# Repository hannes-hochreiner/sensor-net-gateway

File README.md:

# Sensor Net Gateway
A gateway for translating messages from the sensor net sensors to USB CDC.

## Pre-Order PCB Checklist
  * [x] ground flood
  * [x] surround antenna traces with vias
  * [x] change LDO footprint
  * [x] change connector footprint
  * [x] interrupt lines
  * [x] diagram cleanup
  * [x] diagram check
  * [x] layout check

# Post Assembly Checks

## Electrical Check
On visual inspection, the connections looked pretty good.
To make sure nothing major went wrong, I checked for shorts, especially between power and ground.
I also checked that ground was connected to the right side of the electrolytic capacitor.

## FTDI
My first check of the FTDI chip was to simply connect the board and check the output of dmsg:
```
[862594.355360] Indeed it is in host mode hprt0 = 00021501
[862594.565069] usb 1-1: new full-speed USB device number 2 using dwc_otg
[862594.565389] Indeed it is in host mode hprt0 = 00021501
[862594.812139] usb 1-1: New USB device found, idVendor=0403, idProduct=6015, bcdDevice=10.00
[862594.812159] usb 1-1: New USB device strings: Mfr=1, Product=2, SerialNumber=3
[862594.812168] usb 1-1: Product: FT230X Basic UART
[862594.812176] usb 1-1: Manufacturer: FTDI
[862594.812184] usb 1-1: SerialNumber: DM01KPIW
[862594.947315] usbcore: registered new interface driver usbserial_generic
[862594.947420] usbserial: USB Serial support registered for generic
[862594.963184] usbcore: registered new interface driver ftdi_sio
[862594.963293] usbserial: USB Serial support registered for FTDI USB Serial Device
[862594.963573] ftdi_sio 1-1:1.0: FTDI USB Serial Device converter detected
[862594.963800] usb 1-1: Detected FT-X
[862594.997482] usb 1-1: FTDI USB Serial Device converter now attached to ttyUSB0
```
## Power
Next, I checked the power rail after the two-stage conversion.
I got 2.75 V, which is a bit lower than expected, but within specification (2.8 V +/- 3%) and still ok for my use.

## UART communication
UART communication without hardware flow control worked fine, after I switched TX and RX (see [issue TX-RX and CTS-RTS inverted](#TX-RX-and-CTS-RTS-inverted) below).
I have tried running the interface at 10 kHz, 100 kHz, and 1 MHz.
So far, I was only successful at 10 kHz.
My suspicion is that the internal high-speed clock of the STM32 is not precise enough.

## RFM98
The RFM98 works as expected.
The RSSI is around -95 dBm, which is lower than I hoped.
With the breakout board and a different antenna, I have seen a typical RSSI around -65 dBm.
So there is some potential for improvement here by using different antennas.
Since the module claims to have a sensitivity down to -148 dBm, I think I should be fine.
From what I have seen, most of the sensor transmissions were picked up.

## Authentication chip
So far, I have not been able to convince the authentication chip to respond.
I have tried different addresses and also implemented the wake-up sequence.
My suspicion is that I did not properly solder it.

## External oscillator
I could not get a stable signal from the external oscillator.
Probably also a case for re-soldering.

# Issues
## TX-RX and CTS-RTS inverted
When I wired up the schematic, I made the mistake to connect TX to TX, RX to RX, and so on.
While this works fine for SPI and I2C, it does not work for UART.
With UART, TX has to be connected to RX and CTS to RTS.
The saving grace is that the STM32 has an option to swap TX and RX lines.
Seems that I am not the first one to make this mistake :-).

CTS and RTS cannot be swapped in the chip, so in this iteration I won't be able to use the integrated hardware flow control.
Since I am using the UART interface based on interrupts, it should be easily possible to set the RTS and CTS lines manually.

## Cut-outs seem off
The PCB fits fine into the case, but the margins are not uniform.
Therefore, I want to go back and check the cut-outs.

# Hardware to order
## Screws
Self-tapping screws [Amazon link](https://www.amazon.de/Baoyl-Office-Cutting-Tapping-Printer-Accessories/dp/B07VX7XYYC/ref=sr_1_8?__mk_de_DE=%C3%85M%C3%85%C5%BD%C3%95%C3%91&keywords=M3%2Bself-tapping%2Bscrews&qid=1567273654&s=gateway&sr=8-8&th=1)

## Hub
USB-hub [Amazon link](https://www.amazon.de/CSL-aktiver-schaltbar-Verteiler-Notebook/dp/B07F2Q94CT/ref=sr_1_41?__mk_de_DE=%C3%85M%C3%85%C5%BD%C3%95%C3%91&crid=22QNN2JE5YY1E&keywords=usb+hub+aktiv+3.0+mit+netzteil&qid=1567355394&s=gateway&sprefix=usb+hub%2Caps%2C195&sr=8-41)

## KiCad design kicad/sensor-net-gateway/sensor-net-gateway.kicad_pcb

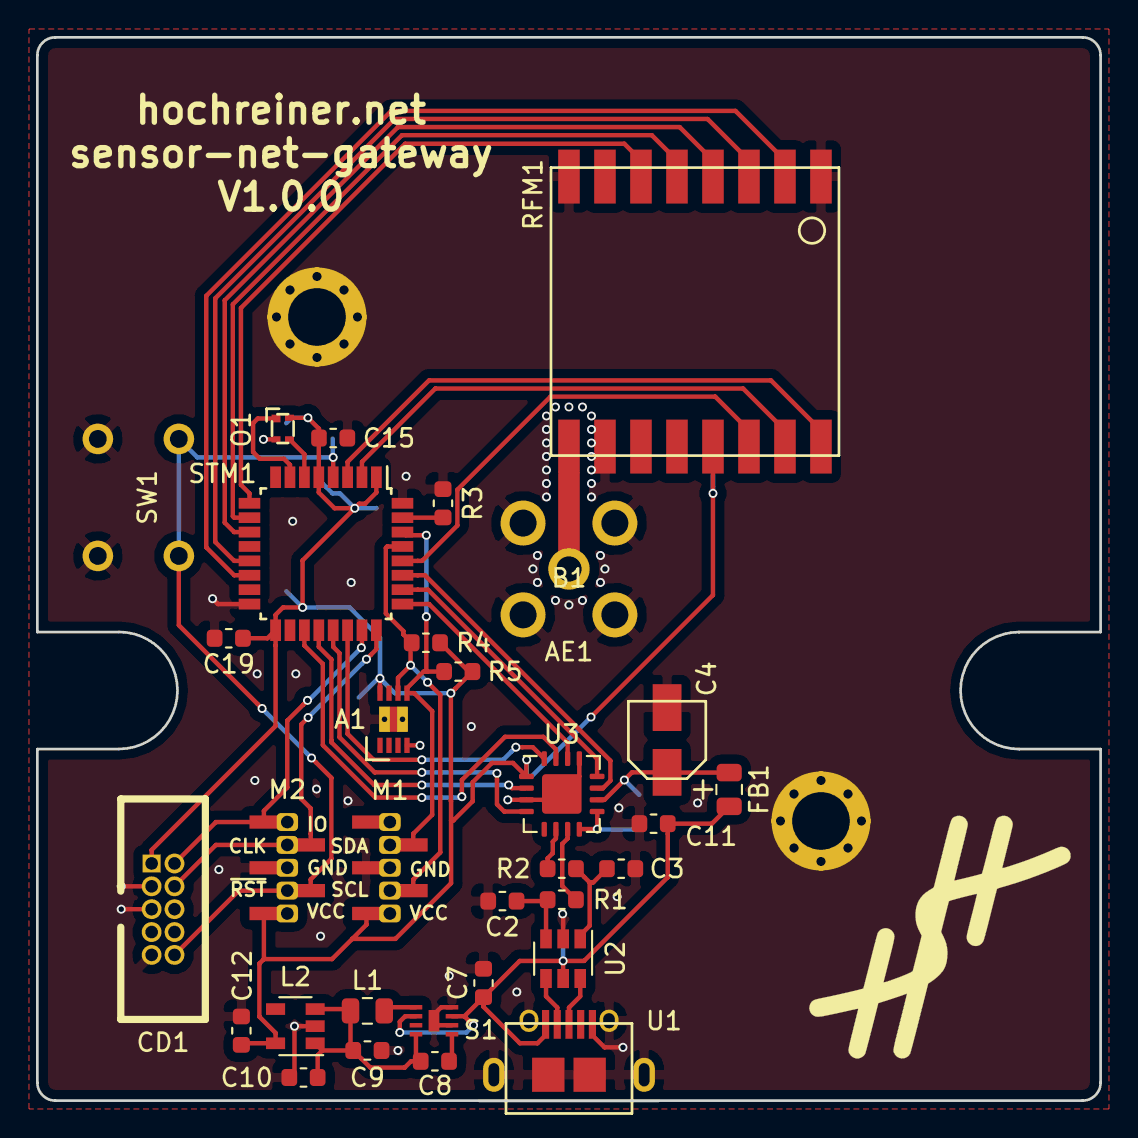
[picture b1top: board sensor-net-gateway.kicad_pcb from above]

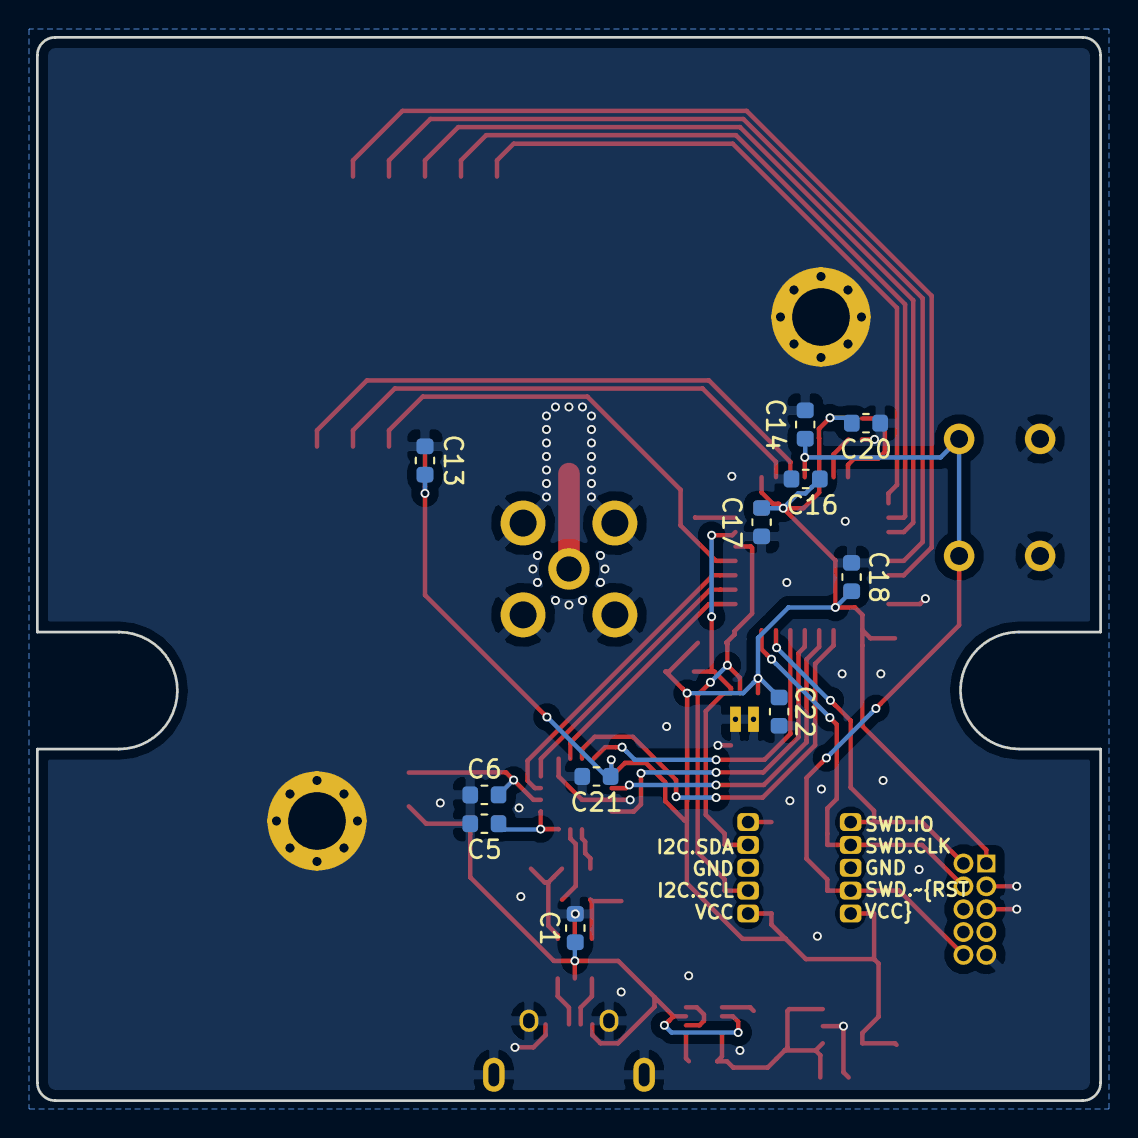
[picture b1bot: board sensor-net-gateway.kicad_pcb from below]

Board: 2 copper layers, 59.1 x 59.1 mm, 45 parts (11 on the bottom side), 38 nets.

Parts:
A1: ATECC508A-MAHCZ-S
AE1: Antenna_Shield; CONSMA001-G
B1: 1593JGY
C1, C5, C6, C13, C14, C16, C17, C18, C20, C21, C22: 0.1µF; C_0603_1608Metric
C2, C3: 47pF; C_0603_1608Metric
C4: 4.7µF; 865080640004
C7, C9: 4.7µF; C_0603_1608Metric
C8: 560pF; C_0603_1608Metric
C10: 0.47µF; C_0603_1608Metric
C11: 10nF; C_0603_1608Metric
C12, C19: 10µF; C_0603_1608Metric
C15: 1µF; C_0603_1608Metric
CD1: CORTEX-DEBUG
FB1: Ferrite_Bead; C_0805_2012Metric
L1: 1µH; L_0805_2012Metric
L2: MIC94310-MYM5-TR; SOT-23-5
L3: logo
M1, M2: M50-3130545
O1: DSC6011HE2A-032.0000
R1, R2: 27R; R_0603_1608Metric
R3, R4, R5: 10k; R_0603_1608Metric
RFM1: RFM98
S1: MIC23050-SYML-TR
STM1: STM32L021K4T6; LQFP-32_7x7mm_P0.8mm
SW1: SW_Push; 1825910-6
U1: USB_micro_ab; MOLEX_USB_MICRO_0475890001
U2: USBLC6-2SC6; SOT-23-6
U3: FT230XQ; QFN-16-1EP_4x4mm_P0.65mm_EP2.7x2.7mm

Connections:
/3V0: A1.8, C12.1, C13.1, C15.1, C16.1, C17.2, C18.1, C19.1, C20.1, C21.1, C22.1, CD1.1, L2.5, M1.1, M2.1, O1.4, R4.2, R5.2, RFM1.13, STM1.1, STM1.5, STM1.17, U3.1
/FTDI_IO0: STM1.26, U3.12
/FTDI_IO1: STM1.27, U3.11
/FTDI_IO3: STM1.25, U3.14
/MCU/I2C.SCL: A1.6, M1.2, R4.1, STM1.29
/MCU/I2C.SDA: A1.5, M1.4, R5.1, STM1.30
/MCU/OSC: O1.3, STM1.6
/MCU/OSC_EN: O1.1, STM1.7
/MCU/SWD_CLK: CD1.4, M2.4, STM1.24
/MCU/SWD_IO: CD1.2, M2.5, STM1.23
/MCU/~SWD_RST: C14.1, CD1.10, M2.2, STM1.4, SW1.2
/RFM_DIO0: RFM1.14, STM1.28
/RFM_DIO1: RFM1.15, STM1.2
/RFM_DIO2: RFM1.16, STM1.3
/RFM_RESET: RFM1.6, STM1.9
/Radio/ANT: AE1.1, RFM1.9
/SPI.MISO: RFM1.2, STM1.14
/SPI.MOSI: RFM1.3, STM1.13
/SPI.SCK: RFM1.4, STM1.11
/SPI.~CS: RFM1.5, STM1.10
/UART.CTS: STM1.21, U3.4
/UART.RTS: STM1.22, U3.16
/UART.RX: STM1.20, U3.2
/UART.TX: STM1.19, U3.15
/VBUS: C1.1, C7.1, C11.1, FB1.2, S1.2, S1.7, U1.1, U2.5
GND: A1.4, AE1.2, B1.1, C1.2, C2.2, C3.2, C4.2, C5.2, C6.1, C7.2, C9.2, C10.2, C11.2, C12.2, C13.2, C14.2, C15.2, C16.2, C17.1, C18.2, C19.2, C20.2, C21.2, C22.2, CD1.3, CD1.5, CD1.9, L2.2, M1.3, M2.3, O1.2, R3.2, RFM1.1, RFM1.8, RFM1.10, S1.6, S1.8, STM1.16, STM1.32, SW1.1, U1.5, U2.2, U3.3, U3.13, U3.17
unnamed: C2.1, R1.2, U2.3
unnamed: C3.1, R2.2, U2.1
unnamed: C4.1, C6.2, FB1.1, U3.10
unnamed: C5.1, U3.8, U3.9
unnamed: C8.2, S1.5
unnamed: C8.1, C9.1, C10.1, L1.2, L2.1, L2.3, S1.4
unnamed: L1.1, S1.1
unnamed: R1.1, U3.7
unnamed: R2.1, U3.6
unnamed: R3.1, STM1.31
unnamed: U1.2, U2.4
unnamed: U1.3, U2.6

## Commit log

2019-09-01 finished initial layout
2019-09-16 added first post assembly checks
2019-09-28 Updated tests
2019-09-28 added test firmware
2019-09-28 set SPI to 8 MHz
2019-09-28 extracted linked list
2019-09-29 moved linked-list to a separate repository
2019-09-29 fixed bug
